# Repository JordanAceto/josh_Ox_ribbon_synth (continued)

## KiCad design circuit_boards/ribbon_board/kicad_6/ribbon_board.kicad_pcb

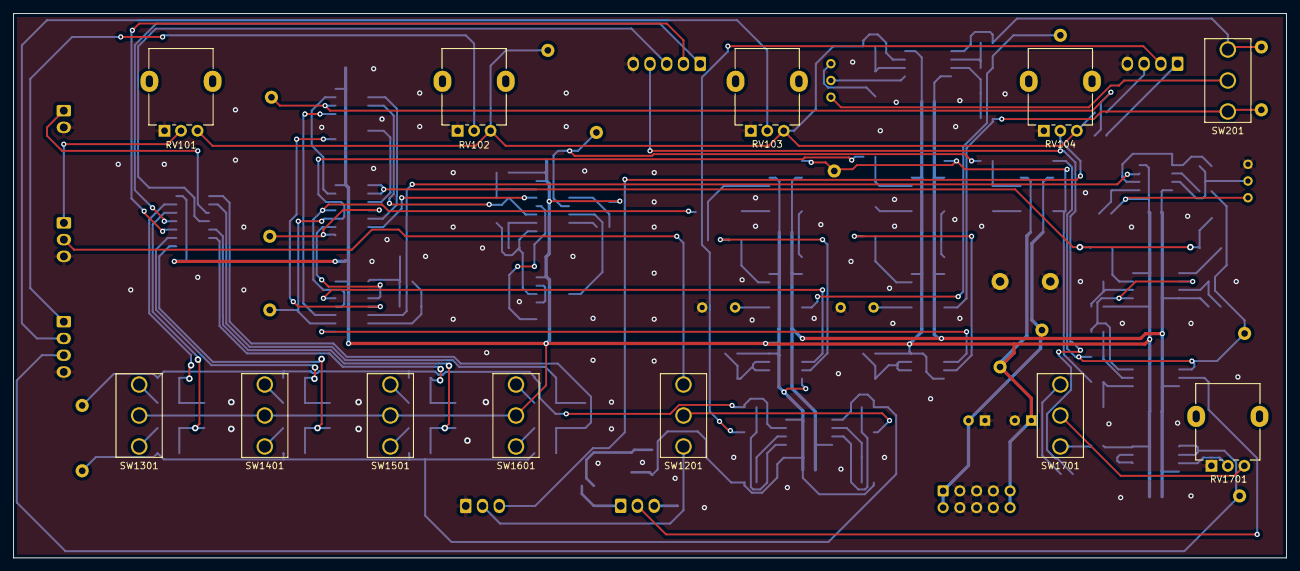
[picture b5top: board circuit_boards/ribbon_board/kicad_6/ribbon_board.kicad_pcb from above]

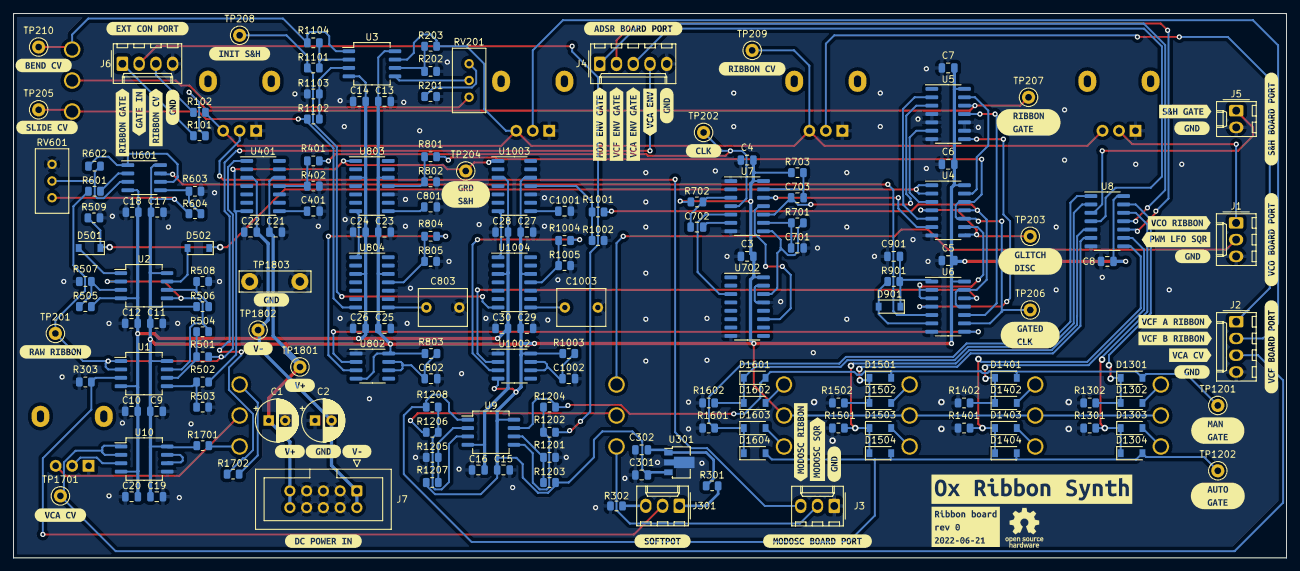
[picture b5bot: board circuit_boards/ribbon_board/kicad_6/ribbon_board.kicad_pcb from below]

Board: 2 copper layers, 193.0 x 82.5 mm, 229 parts (217 on the bottom side), 115 nets.

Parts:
C1, C2: 10u; CP_Radial_D6.3mm_P2.50mm
C3, C4, C5, C6, C7, C8, C9, C10, C11, C12, C13, C14, C15, C16, C17, C18, C19, C20, C21, C22, C23, C24, C25, C26, C27, C28, C29, C30, C302: 100n; C_0805_2012Metric
C301: 470n; C_0805_2012Metric
C401, C801, C1001: 2n2; C_0805_2012Metric
C701: 1n; C_0805_2012Metric
C702, C703: 4n7; C_0805_2012Metric
C802, C901, C1002: 10n; C_0805_2012Metric
C803, C1003: 1u; C_Rect_L7.2mm_W5.5mm_P5.00mm_FKS2_FKP2_MKS2_MKP2
D501, D502, D901, D1301, D1302, D1303, D1304, D1401, D1402, D1403, D1404, D1501, D1502, D1503, D1504, D1601, D1602, D1603, D1604: 1N4148W; D_SOD-123
J1: VCO_port; Molex_KK-254_AE-6410-03A_1x03_P2.54mm_Vertical
J2: VCF_port; Molex_KK-254_AE-6410-04A_1x04_P2.54mm_Vertical
J3: mod_osc_port; Molex_KK-254_AE-6410-03A_1x03_P2.54mm_Vertical
J4: ADSR_port; Molex_KK-254_AE-6410-05A_1x05_P2.54mm_Vertical
J5: S&H_port; Molex_KK-254_AE-6410-02A_1x02_P2.54mm_Vertical
J6: ext_port; Molex_KK-254_AE-6410-04A_1x04_P2.54mm_Vertical
J7: power_entry; IDC-Header_2x05_P2.54mm_Vertical
J301: ribbon; Molex_KK-254_AE-6410-03A_1x03_P2.54mm_Vertical
R101, R102: 1k; R_0805_2012Metric
R201, R603, R702, R703, R1201, R1202, R1205, R1206: 10k; R_0805_2012Metric
R202, R203, R303, R501, R502, R503, R504, R509, R601, R602, R604, R701, R1101, R1102, R1103, R1104, R1203, R1207, R1301, R1302, R1401, R1402, R1501, R1502, R1601, R1602, R1702: 100k; R_0805_2012Metric
R301, R302: 4k7; R_0805_2012Metric
R401, R801, R804, R1001, R1004: 5k6; R_0805_2012Metric
R402, R802, R805, R1002, R1005: 1k8; R_0805_2012Metric
R505, R506, R1701: 150k; R_0805_2012Metric
R507, R508: 470; R_0805_2012Metric
R803, R1003, R1204, R1208: 1M2; R_0805_2012Metric
R901: 120k; R_0805_2012Metric
RV101, RV102, RV103, RV104: 100k c.d.; Potentiometer_Alpha_RD901F-40-00D_Single_Vertical
RV201, RV601: 100k; Potentiometer_Bourns_3296W_Vertical
RV1701: 100k A; Potentiometer_Alpha_RD901F-40-00D_Single_Vertical
SW201, SW1201, SW1701: SW_SPDT; SPDT_mini_toggle
SW1301, SW1401, SW1501, SW1601: SW_SPDT_MSM; SPDT_mini_toggle
TP201: raw_ribbon; TestPoint_Keystone_5000-5004_Miniature
TP202: clk; TestPoint_Keystone_5000-5004_Miniature
TP203: glitch_dis; TestPoint_Keystone_5000-5004_Miniature
TP204: guard_s_and_h; TestPoint_Keystone_5000-5004_Miniature
TP205: slide_s_and_h; TestPoint_Keystone_5000-5004_Miniature
TP206: gated_clk; TestPoint_Keystone_5000-5004_Miniature
TP207: gate; TestPoint_Keystone_5000-5004_Miniature
TP208: init_s_and_h; TestPoint_Keystone_5000-5004_Miniature
TP209: ribbon_cv; TestPoint_Keystone_5000-5004_Miniature
TP210: bend_cv; TestPoint_Keystone_5000-5004_Miniature
TP1201: man_gate; TestPoint_Keystone_5000-5004_Miniature
TP1202: audo_gate; TestPoint_Keystone_5000-5004_Miniature
TP1701: vca_cv; TestPoint_Keystone_5000-5004_Miniature
TP1801: V+; TestPoint_Keystone_5000-5004_Miniature
TP1802: V-; TestPoint_Keystone_5000-5004_Miniature
TP1803: GND; TestPoint_Bridge_Pitch7.62mm_Drill1.3mm
U1, U2, U3, U9, U10: TL072; SO-8_5.3x6.2mm_P1.27mm
U4, U8: 4081; SOIC-14_3.9x8.7mm_P1.27mm
U5: 4013; SOIC-14_3.9x8.7mm_P1.27mm
U6, U7: 40106; SOIC-14_3.9x8.7mm_P1.27mm
U301: L78L10_SOT89; SOT-89-3
U401, U803, U804, U1003, U1004: LF398_SOIC14; SOIC-14_3.9x8.7mm_P1.27mm
U601: LM358; SOIC-8_3.9x4.9mm_P1.27mm
U702: 4017; SOIC-16_3.9x9.9mm_P1.27mm
U802, U1002: TLC555xD; SOIC-8_3.9x4.9mm_P1.27mm
kibuzzard-62AC7A9F: G***; kibuzzard-62AC7A9F
kibuzzard-62B1F2D1, kibuzzard-62B1F2D1#2, kibuzzard-62B1F2D1#3, kibuzzard-62B1F2D1#4, kibuzzard-62B1F2D1#5, kibuzzard-62B1F2D1#6, kibuzzard-62B1F2D1#7, kibuzzard-62B1F2D1#8: G***; kibuzzard-62B1F2D1
kibuzzard-62B1F3ED: G***; kibuzzard-62B1F3ED
kibuzzard-62B1F4B1: G***; kibuzzard-62B1F4B1
kibuzzard-62B1F4C1: G***; kibuzzard-62B1F4C1
kibuzzard-62B1F7DB: G***; kibuzzard-62B1F7DB
kibuzzard-62B1F7F1: G***; kibuzzard-62B1F7F1
kibuzzard-62B1F8A8: G***; kibuzzard-62B1F8A8
kibuzzard-62B1F8CB: G***; kibuzzard-62B1F8CB
kibuzzard-62B1F8F4: G***; kibuzzard-62B1F8F4
kibuzzard-62B1F9D0: G***; kibuzzard-62B1F9D0
kibuzzard-62B1F45D: G***; kibuzzard-62B1F45D
kibuzzard-62B1F49A: G***; kibuzzard-62B1F49A
kibuzzard-62B1F53B: G***; kibuzzard-62B1F53B
kibuzzard-62B1F72D: G***; kibuzzard-62B1F72D
kibuzzard-62B1F77F: G***; kibuzzard-62B1F77F
kibuzzard-62B1F525: G***; kibuzzard-62B1F525
kibuzzard-62B1F567: G***; kibuzzard-62B1F567
kibuzzard-62B1F712: G***; kibuzzard-62B1F712
kibuzzard-62B1F743: G***; kibuzzard-62B1F743
kibuzzard-62B1F752: G***; kibuzzard-62B1F752
kibuzzard-62B1F821: G***; kibuzzard-62B1F821
kibuzzard-62B1F904: G***; kibuzzard-62B1F904
kibuzzard-62B1F917: G***; kibuzzard-62B1F917
kibuzzard-62B1F959, kibuzzard-62B1F959#2: G***; kibuzzard-62B1F959
kibuzzard-62B1F963, kibuzzard-62B1F963#2: G***; kibuzzard-62B1F963
kibuzzard-62B1FC16: G***; kibuzzard-62B1FC16
kibuzzard-62B1FC43: G***; kibuzzard-62B1FC43
kibuzzard-62B1FC58: G***; kibuzzard-62B1FC58
kibuzzard-62B1FC81: G***; kibuzzard-62B1FC81
kibuzzard-62B1FCCC: G***; kibuzzard-62B1FCCC
kibuzzard-62B1FD45: G***; kibuzzard-62B1FD45
kibuzzard-62B1FD51: G***; kibuzzard-62B1FD51
kibuzzard-62B1FD62: G***; kibuzzard-62B1FD62
kibuzzard-62B1FDDB: G***; kibuzzard-62B1FDDB
kibuzzard-62B1FE6D: G***; kibuzzard-62B1FE6D
kibuzzard-62B1FEB0: G***; kibuzzard-62B1FEB0
kibuzzard-62B1FECC: G***; kibuzzard-62B1FECC
kibuzzard-62B235EB: G***; kibuzzard-62B235EB
kibuzzard-62B239A3: G***; kibuzzard-62B239A3
kibuzzard-62B23681: G***; kibuzzard-62B23681

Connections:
+15V: C1.1, C3.1, C4.1, C5.1, C6.1, C7.1, C8.1, C9.1, C11.1, C13.1, C15.1, C17.1, C19.1, C21.1, C23.1, C25.1, C27.1, C29.1, C301.1, J7.9, J7.10, R506.1, R604.2, R702.1, R703.1, R803.1, R1003.1, R1203.2, R1207.2, R1701.1, RV601.3, SW1301.2, SW1401.2, SW1501.2, SW1601.2, TP1801.1, U1.8 (V+), U2.8 (V+), U3.8 (V+), U4.14 (VDD), U5.14 (VDD), U6.14 (VDD), U7.14 (VDD), U8.14 (VDD), U9.8 (V+), U10.8 (V+), U301.3 (IN), U401.12 (V+), U601.8 (V+), U702.16 (VDD), U802.4 (R), U802.8 (VCC), U803.12 (V+), U804.12 (V+), U1002.4 (R), U1002.8 (VCC), U1003.12 (V+), U1004.12 (V+)
-15V: C2.2, C10.2, C12.2, C14.2, C16.2, C18.2, C20.2, C22.2, C24.2, C26.2, C28.2, C30.2, J7.1, J7.2, R505.2, TP1802.1, U1.4 (V-), U2.4 (V-), U3.4 (V-), U9.4 (V-), U10.4 (V-), U401.3 (V-), U601.4 (V-), U803.3 (V-), U804.3 (V-), U1003.3 (V-), U1004.3 (V-)
/GATE_IN: J6.2, R1202.1
/MOD_OSC_RIBBON_CTL: J3.3, RV104.2
/MOD_OSC_SQR: J3.2, SW1201.1 (A)
/PWM_LFO_SQR: J1.2, SW1201.3 (C)
/RIBBON_CV: R102.2, R203.2, RV101.3, RV102.3, RV103.3, RV104.3, TP209.1, U3.7
/RIBBON_GATE: R101.2, TP207.1, U5.12 (~Q)
/VCA_ADSR: J4.4, R1702.1
/VCA_CV: J2.3, TP1701.1, U10.1, U10.2 (-)
/VCF_A_RIBBON_CTL: J2.1, RV102.2
/VCF_B_RIBBON_CTL: J2.2, RV103.2
/VCO_RIBBON_CTL: J1.1, RV101.2
/gate_controller/MOD_ENV_GATE: J4.1, U8.11
/gate_controller/S&H_GATE: J5.1, U8.3
/gate_controller/VCA_ADSR_gate_logic/AUTO_GATE: D1304.2 (A), D1404.2 (A), D1504.2 (A), D1604.2 (A), R1208.2, TP1202.1, U9.1
/gate_controller/VCA_ADSR_gate_logic/RIBBON_GATE: D1301.2 (A), D1401.2 (A), D1501.2 (A), D1601.2 (A), R1204.2, TP1201.1, U9.7
/gate_controller/VCA_ENV_GATE: J4.3, U8.4
/gate_controller/VCF_ENV_GATE: J4.2, U8.10
/ribbon_controller/BEND_CV: R1104.2, SW201.3 (C), TP210.1, U3.1
/ribbon_controller/SLIDE_CV: R1102.1, SW201.1 (A), TP205.1, U804.7
/ribbon_controller/TRIG_0: R401.1, TP202.1, U7.4
/ribbon_controller/TRIG_9: U4.6, U7.12
/ribbon_controller/bend_scaler/INIT_IN: R1101.1, TP208.1, U1004.7
/ribbon_controller/comparator/COMP_OUT: U6.5, U601.7
/ribbon_controller/comparator/SIGNAL_IN: R501.1, R601.1, TP201.1, U1.1, U1.2 (-), U401.1 (I)
/ribbon_controller/gate_conditioner/GATED_CLK: R801.1, TP206.1, U4.10, U4.12, U6.9
/ribbon_controller/gate_conditioner/GD_IN: TP203.1, U4.4, U4.8
/ribbon_controller/gate_conditioner/S&H_TRIG: R1001.1, U4.11, U6.11, U6.13
/ribbon_controller/glitch_discriminator/S&H_RIBBON: R502.1, TP204.1, U401.7, U803.1 (I), U1003.1 (I)
/ribbon_controller/~CLK_9: C703.1, U5.3 (C), U7.10
GND: C1.2, C2.1, C3.2, C4.2, C5.2, C6.2, C7.2, C8.2, C9.2, C10.1, C11.2, C12.1, C13.2, C14.1, C15.2, C16.1, C17.2, C18.1, C19.2, C20.1, C21.2, C22.1, C23.2, C24.1, C25.2, C26.1, C27.2, C28.1, C29.2, C30.1, C301.2, C302.2, C401.2, C701.2, C801.2, C802.2, C803.2, C901.2, C1001.2, C1002.2, C1003.2, J1.3, J2.4, J3.1, J4.5, J5.2, J6.4, J7.3, J7.4, J7.5, J7.6, J7.7, J7.8, R201.2, R202.1, R302.2, R303.2, R402.2, R503.2, R507.1, R508.2, R509.2, R603.1, R802.2, R805.2, R1002.2, R1005.2, R1103.1, R1201.1, R1205.1, R1301.2, R1302.2, R1401.2, R1402.2, R1501.2, R1502.2, R1601.2, R1602.2, RV101.1, RV102.1, RV103.1, RV104.1, RV601.1, RV1701.1, TP1803.1, U4.7 (VSS), U5.4 (R), U5.5 (D), U5.7 (VSS), U5.9 (D), U5.10 (R), U6.7 (VSS), U7.1, U7.7 (VSS), U8.7 (VSS), U10.5 (+), U301.2 (GND), U401.10 (T), U702.8 (VSS), U702.13 (CKEN), U702.15 (Reset), U802.1 (GND), U803.10 (T), U804.10 (T), U1002.1 (GND), U1003.10 (T), U1004.10 (T)
unnamed: C302.1, R301.1, U301.1 (OUT)
unnamed: C401.1, U401.8 (Ch)
unnamed: C701.1, R701.1, U7.9
unnamed: C702.1, U7.6
unnamed: C702.2, R702.2, U7.3
unnamed: C703.2, R703.2, U7.13
unnamed: C801.1, U803.8 (Ch)
unnamed: C802.1, R803.2, U802.6 (THR), U802.7 (DIS)
unnamed: C803.1, U804.8 (Ch)
unnamed: C901.1, D901.1 (K), R901.2, U6.1
unnamed: C1001.1, U1003.8 (Ch)
unnamed: C1002.1, R1003.2, U1002.6 (THR), U1002.7 (DIS)
unnamed: C1003.1, U1004.8 (Ch)
unnamed: D501.1 (K), D502.1 (K), R509.1, U4.1, U4.2
unnamed: D501.2 (A), U2.1
unnamed: D502.2 (A), U2.7
unnamed: D901.2 (A), R901.1, U6.6
unnamed: D1301.1 (K), D1302.1 (K), R1302.1, U8.13
unnamed: D1302.2 (A), SW1301.3
unnamed: D1303.1 (K), D1304.1 (K), R1301.1, U8.12
unnamed: D1303.2 (A), SW1301.1
unnamed: D1401.1 (K), D1402.1 (K), R1402.1, U8.9
unnamed: D1402.2 (A), SW1401.3
unnamed: D1403.1 (K), D1404.1 (K), R1401.1, U8.8
unnamed: D1403.2 (A), SW1401.1
unnamed: D1501.1 (K), D1502.1 (K), R1502.1, U8.6
unnamed: D1502.2 (A), SW1501.3
unnamed: D1503.1 (K), D1504.1 (K), R1501.1, U8.5
unnamed: D1503.2 (A), SW1501.1
unnamed: D1601.1 (K), D1602.1 (K), R1602.1, U8.2
unnamed: D1602.2 (A), SW1601.3
unnamed: D1603.1 (K), D1604.1 (K), R1601.1, U8.1
unnamed: D1603.2 (A), SW1601.1
unnamed: J6.1, R101.1
unnamed: J6.3, R102.1
unnamed: J301.1, R301.2
unnamed: J301.2, R303.1, U1.3 (+)
unnamed: J301.3, R302.1
unnamed: R201.1, RV201.1
unnamed: R202.2, R203.1, U3.6 (-)
unnamed: R401.2, R402.1, U401.11 (Hold)
unnamed: R501.2, R504.1, U1.6 (-)
unnamed: R502.2, R503.1, U1.5 (+)
unnamed: R504.2, U1.7, U2.2 (-), U2.5 (+)
unnamed: R505.1, R507.2, U2.3 (+)
unnamed: R506.2, R508.1, U2.6 (-)
unnamed: R601.2, U601.2 (-)
unnamed: R602.1, RV601.2, U601.3 (+)
unnamed: R602.2, U601.1, U601.6 (-)
unnamed: R603.2, R604.1, U601.5 (+)
unnamed: R701.2, U7.8, U702.14 (CLK)
unnamed: R801.2, R802.1, U803.11 (Hold)
unnamed: R804.1, U802.3 (Q)
unnamed: R804.2, R805.1, U804.11 (Hold)
unnamed: R1001.2, R1002.1, U1003.11 (Hold)
unnamed: R1004.1, U1002.3 (Q)
unnamed: R1004.2, R1005.1, U1004.11 (Hold)
unnamed: R1101.2, R1104.1, U3.2 (-)
unnamed: R1102.2, R1103.2, U3.3 (+)
unnamed: R1201.2, R1203.1, U9.6 (-)
unnamed: R1202.2, R1204.1, U9.5 (+)
unnamed: R1205.2, R1207.1, U9.2 (-)
unnamed: R1206.1, SW1201.2 (B)
unnamed: R1206.2, R1208.1, U9.3 (+)
unnamed: R1701.2, SW1701.1 (A)
unnamed: R1702.2, SW1701.3 (C)
unnamed: RV201.2, U3.5 (+)
unnamed: RV201.3, SW201.2 (B)
unnamed: RV1701.2, U10.3 (+)
unnamed: RV1701.3, SW1701.2 (B)
unnamed: U4.3, U5.6 (S)
unnamed: U4.5, U5.2 (~Q)
unnamed: U4.9, U6.2, U6.3
unnamed: U4.13, U5.13 (Q)
unnamed: U5.8 (S), U6.4
unnamed: U5.11 (C), U6.10
unnamed: U6.8, U802.2 (TR)
unnamed: U7.5, U702.3 (Q0)
unnamed: U7.11, U702.11 (Q9)
unnamed: U10.6 (-), U10.7
unnamed: U803.7, U804.1 (I)
unnamed: U6.12, U1002.2 (TR)
unnamed: U1003.7, U1004.1 (I)

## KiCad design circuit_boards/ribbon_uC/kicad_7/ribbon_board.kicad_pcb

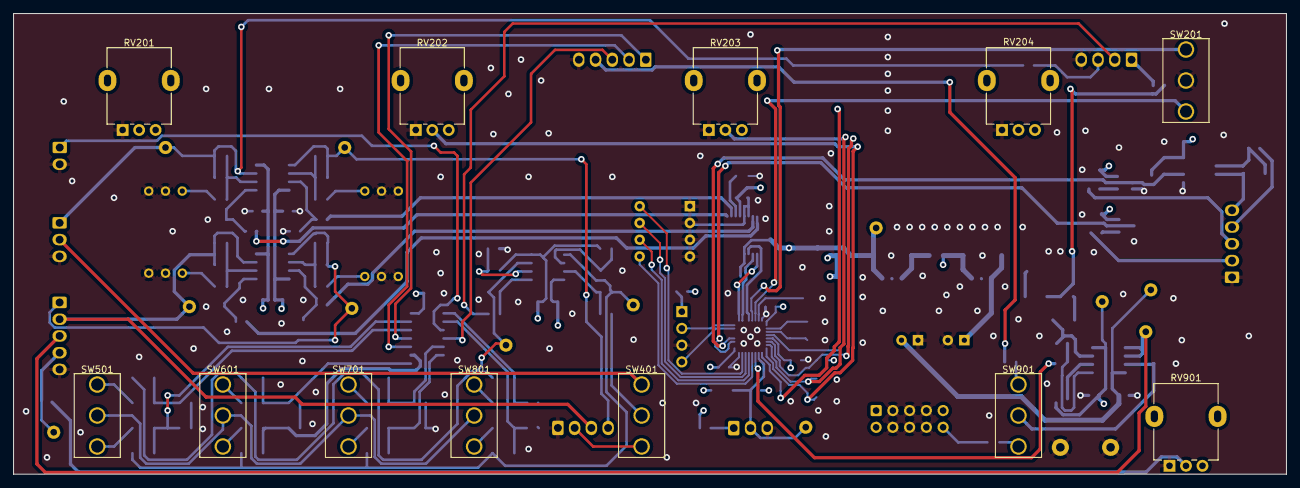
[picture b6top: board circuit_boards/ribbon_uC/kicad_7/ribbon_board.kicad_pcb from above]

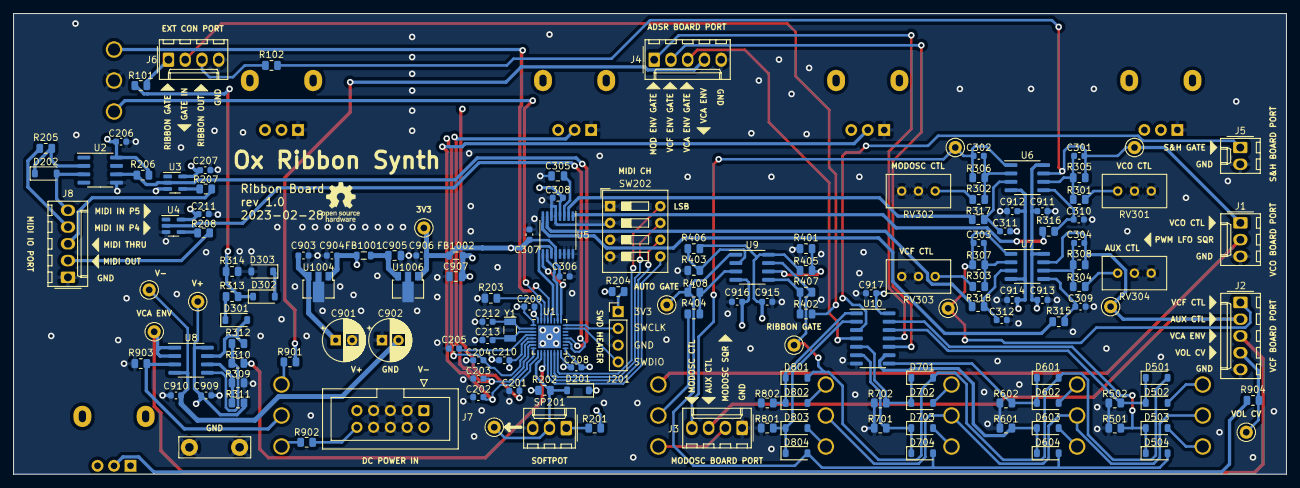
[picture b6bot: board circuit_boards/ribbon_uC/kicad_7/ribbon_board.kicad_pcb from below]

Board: 4 copper layers, 193.0 x 69.8 mm, 165 parts (153 on the bottom side), 105 nets.

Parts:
C201, C202, C203, C204, C205, C206, C207, C208, C209, C210, C211, C301, C302, C303, C304, C306, C307, C308, C309, C310, C311, C312, C903, C904, C906, C909, C910, C911, C912, C913, C914, C915, C916, C917: 100n; C_0603_1608Metric
C212, C213: 4p3; C_0603_1608Metric
C305, C907: 1u; C_0805_2012Metric
C901, C902: 10u; CP_Radial_D6.3mm_P2.50mm
C905: 2u2; C_0805_2012Metric
D201: DNF; D_SOD-123
D202, D301, D501, D502, D503, D504, D601, D602, D603, D604, D701, D702, D703, D704, D801, D802, D803, D804: 1N4148W; D_SOD-123
D302, D303: 5v1; D_SOD-123
FB1001, FB1002: 100R @ 100MHz; L_0805_2012Metric
J1: VCO_port; Molex_KK-254_AE-6410-03A_1x03_P2.54mm_Vertical
J2: VCF_port; Molex_KK-254_AE-6410-05A_1x05_P2.54mm_Vertical
J3: mod_osc_port; Molex_KK-254_AE-6410-04A_1x04_P2.54mm_Vertical
J4: ADSR_port; Molex_KK-254_AE-6410-05A_1x05_P2.54mm_Vertical
J5: S&H_port; Molex_KK-254_AE-6410-02A_1x02_P2.54mm_Vertical
J6: ext_port; Molex_KK-254_AE-6410-04A_1x04_P2.54mm_Vertical
J7: power_entry; IDC-Header_2x05_P2.54mm_Vertical
J8: MIDI_IO_port; Molex_KK-254_AE-6410-05A_1x05_P2.54mm_Vertical
J201: SWD_header; PinHeader_1x04_P2.54mm_Vertical
R101, R102, R204, R313, R904: 1k; R_0805_2012Metric
R201: 22; R_0805_2012Metric
R202: DNF; R_0805_2012Metric
R203, R206, R309, R310, R401, R402, R403, R404: 10k; R_0805_2012Metric
R205: 220; R_0805_2012Metric
R207, R208: 47; R_0805_2012Metric
R301, R302, R303, R304: 4k7; R_0805_2012Metric
R305, R306, R307, R308, R315, R316, R317, R318: 12k; R_0805_2012Metric
R311, R314, R405, R406, R501, R502, R601, R602, R701, R702, R801, R802, R903: 100k; R_0805_2012Metric
R312, R407, R408: 1M2; R_0805_2012Metric
R901: 82k; R_0805_2012Metric
R902: 200k; R_0805_2012Metric
RV201, RV204: 10k; Potentiometer_Alpha_RD901F-40-00D_Single_Vertical
RV202, RV203: 10k c.d.; Potentiometer_Alpha_RD901F-40-00D_Single_Vertical
RV301, RV302, RV303, RV304: 5k; Potentiometer_Bourns_3296W_Vertical
RV901: 100k; Potentiometer_Alpha_RD901F-40-00D_Single_Vertical
SP201: softpot; Molex_KK-254_AE-6410-03A_1x03_P2.54mm_Vertical
SW201, SW501, SW601, SW701, SW801: SW_SPDT_MSM; SPDT_mini_toggle
SW202: MIDI_CH; SW_DIP_SPSTx04_Slide_9.78x12.34mm_W7.62mm_P2.54mm
SW401, SW901: SW_SPDT; SPDT_mini_toggle
TP201: RAW_RIBBON; TestPoint_Keystone_5000-5004_Miniature
TP301: VCO_RIBBON; TestPoint_Keystone_5000-5004_Miniature
TP302: MODOSC_RIBBON; TestPoint_Keystone_5000-5004_Miniature
TP303: VCF_RIBBON; TestPoint_Keystone_5000-5004_Miniature
TP304: AUX_CV; TestPoint_Keystone_5000-5004_Miniature
TP401: rib_gate; TestPoint_Keystone_5000-5004_Miniature
TP402: auto_gate; TestPoint_Keystone_5000-5004_Miniature
TP901: VCA_ADSR_CV; TestPoint_Keystone_5000-5004_Miniature
TP902: VCA_VOL_CV; TestPoint_Keystone_5000-5004_Miniature
TP1001: V+; TestPoint_Keystone_5000-5004_Miniature
TP1002: V-; TestPoint_Keystone_5000-5004_Miniature
TP1003: GND; TestPoint_Bridge_Pitch7.62mm_Drill1.3mm
TP1004: 3v3; TestPoint_Keystone_5000-5004_Miniature
U1: STM32L412K8Ux; QFN-32-1EP_5x5mm_P0.5mm_EP3.45x3.45mm
U2: VO0600T; SOIC-8_3.9x4.9mm_P1.27mm
U3, U4: SN74LV1T34DBV; SOT-23-5
U5: DAC8164; TSSOP-16_4.4x5mm_P0.65mm
U6, U7, U8, U9: TL072; SOIC-8_3.9x4.9mm_P1.27mm
U10: 4081; SOIC-14_3.9x8.7mm_P1.27mm
U1004: L78L05_SOT89; SOT-89-3
U1006: L78L33_SOT89; SOT-89-3
Y1: 32_768KHZ; Crystal_SMD_MicroCrystal_CC7V-T1A-2Pin_3.2x1.5mm

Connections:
+3.3V: C206.1, C207.1, C208.1, C209.1, C211.1, C306.1, C307.1, C906.1, D201.1 (K), FB1002.1, R204.1, R206.1, TP1004.1, U1.1 (VDD), U1.17 (VDD), U2.8 (VCC), U3.5 (VCC), U4.5 (VCC), U5.12 (IOVDD), U1006.1 (OUT)
+3.3VA: C210.1, C308.1, C907.1, FB1002.2, R201.1, RV201.3, RV202.3, RV203.3, RV204.3, U1.5 (VDDA), U5.4 (AVDD)
+5V: C904.1, FB1001.1, R202.1, RV901.3, U1004.1 (OUT)
+15V: C901.1, C903.1, C909.1, C911.1, C913.1, C915.1, C917.1, J7.9, J7.10, R311.2, R405.2, R406.2, R902.1, SW501.2, SW601.2, SW701.2, SW801.2, TP1001.1, U6.8 (V+), U7.8 (V+), U8.8 (V+), U9.8 (V+), U10.14 (VDD), U1004.3 (IN)
-15V: C902.2, C910.2, C912.2, C914.2, C916.2, J7.1, J7.2, TP1002.1, U6.4 (V-), U7.4 (V-), U8.4 (V-), U9.4 (V-)
/EXT_GATE_IN_NORMAL_TO_RIBBON_GATE: J6.2, R402.1
/MOD_OSC_SQR: J3.2, SW401.1 (A)
/OPT_VCF_BBD_CV: C304.2, J2.2, J3.3, R308.2, TP304.1, U7.7
/PWM_LFO_SQR: J1.2, SW401.3 (C)
/VCA_ADSR: J4.4, R901.1
/VCA_ENV_CV: J2.3, TP901.1, U8.1, U8.2 (-)
/VCA_VOL_CV: J2.4, R904.2, TP902.1
/VCO_RIBBON_CTL: C301.2, J1.1, R102.2, R305.2, TP301.1, U6.7
/digital_ribbon_control/GATE_3V3: R310.1, U1.11 (PA5)
/digital_ribbon_control/GLIDE_CV: C204.1, RV204.2, U1.6 (PA0)
/digital_ribbon_control/MIDI_CH_0: SW202.8, U1.15 (PB1)
/digital_ribbon_control/MIDI_CH_1: SW202.7, U1.14 (PB0)
/digital_ribbon_control/MIDI_CH_2: SW202.6, U1.13 (PA7)
/digital_ribbon_control/MIDI_CH_3: SW202.5, U1.12 (PA6)
/digital_ribbon_control/MIDI_IN_P4: J8.4, R205.1
/digital_ribbon_control/MIDI_IN_P5: D202.2 (A), J8.5, U2.3 (C)
/digital_ribbon_control/MIDI_OUT: J8.2, R208.2
/digital_ribbon_control/MIDI_RX: R206.2, U1.20 (PA10), U2.6 (VO), U3.2 (A)
/digital_ribbon_control/MIDI_THRU: J8.3, R207.2
/digital_ribbon_control/MIDI_TX: U1.19 (PA9), U4.2 (A)
/digital_ribbon_control/MODE_SW_1: SW201.1, U1.29 (PB6)
/digital_ribbon_control/MODE_SW_2: SW201.3, U1.30 (PB7)
/digital_ribbon_control/MODOSC_LEV: C202.1, RV202.2, U1.8 (PA2)
/digital_ribbon_control/RAW_RIBBON: D201.2 (A), R202.2, SP201.2, TP201.1, U1.10 (PA4)
/digital_ribbon_control/SPI_CS: U1.25 (PA15), U5.9 (~SYNC)
/digital_ribbon_control/SPI_SCK: U1.26 (PB3), U5.10 (SCLK)
/digital_ribbon_control/SPI_SDO: U1.28 (PB5), U5.11 (DIN)
/digital_ribbon_control/SYS_SWCLK: J201.2, U1.24 (PA14)
/digital_ribbon_control/SYS_SWDIO: J201.4, U1.23 (PA13)
/digital_ribbon_control/VCF_LEV: C203.1, RV203.2, U1.7 (PA1)
/digital_ribbon_control/VCO_LEV: C201.1, RV201.2, U1.9 (PA3)
/gate_controller/MOD_ENV_GATE: J4.1, U10.11
/gate_controller/S&H_GATE: J5.1, U10.3
/gate_controller/VCA_ADSR_gate_logic/AUTO_GATE: D504.2 (A), D604.2 (A), D704.2 (A), D804.2 (A), R408.2, TP402.1, U9.1
/gate_controller/VCA_ADSR_gate_logic/RIBBON_GATE: D501.2 (A), D601.2 (A), D701.2 (A), D801.2 (A), R407.2, TP401.1, U9.7
/gate_controller/VCA_ENV_GATE: J4.3, U10.4
/gate_controller/VCF_ENV_GATE: J4.2, U10.10
/ribbon_scalers/GATE: D302.1 (K), R101.2, R313.2, R314.1
/ribbon_scalers/MODOSC_CTL_OUT: C302.2, J3.4, R306.2, TP302.1, U6.1
/ribbon_scalers/VCF_CTL_OUT: C303.2, J2.1, R307.2, TP303.1, U7.1
GND: C201.2, C202.2, C203.2, C204.2, C205.1, C206.2, C207.2, C208.2, C209.2, C210.2, C211.2, C212.1, C213.1, C305.2, C306.2, C307.2, C308.2, C309.1, C310.1, C311.1, C312.1, C901.2, C902.1, C903.2, C904.2, C905.2, C906.2, C907.2, C909.2, C910.1, C911.2, C912.1, C913.2, C914.1, C915.2, C916.1, C917.2, D303.2 (A), J1.3, J2.5, J3.1, J4.5, J5.2, J6.4, J7.3, J7.4, J7.5, J7.6, J7.7, J7.8, J8.1, J201.3, R203.1, R309.1, R314.2, R401.1, R403.1, R501.2, R502.2, R601.2, R602.2, R701.2, R702.2, R801.2, R802.2, R903.1, RV201.1, RV202.1, RV203.1, RV204.1, RV301.2, RV301.3, RV302.2, RV302.3, RV303.2, RV303.3, RV304.2, RV304.3, RV901.1, SP201.3, SW201.2, SW202.1, SW202.2, SW202.3, SW202.4, TP1003.1, U1.16 (VSS), U1.32 (VSS), U1.33 (VSS), U2.5 (GND), U3.3 (GND), U4.3 (GND), U5.5 (VREFL), U5.6 (GND), U5.13 (A0), U5.14 (A1), U5.15 (~ENABLE), U5.16 (LDAC), U10.7 (VSS), U1004.2 (GND), U1006.2 (GND)
unnamed: C905.1, FB1001.2, U1006.3 (IN)
unnamed: D202.1 (K), R205.2, U2.2 (A)
unnamed: D301.2 (A), R312.2, U8.7
unnamed: D301.1 (K), R313.1
unnamed: D302.2 (A), D303.1 (K)
unnamed: D501.1 (K), D502.1 (K), R502.1, U10.12
unnamed: D502.2 (A), SW501.3
unnamed: D503.2 (A), SW501.1
unnamed: D503.1 (K), D504.1 (K), R501.1, U10.13
unnamed: D601.1 (K), D602.1 (K), R602.1, U10.8
unnamed: D602.2 (A), SW601.3
unnamed: D603.2 (A), SW601.1
unnamed: D603.1 (K), D604.1 (K), R601.1, U10.9
unnamed: D701.1 (K), D702.1 (K), R702.1, U10.5
unnamed: D702.2 (A), SW701.3
unnamed: D703.2 (A), SW701.1
unnamed: D703.1 (K), D704.1 (K), R701.1, U10.6
unnamed: D801.1 (K), D802.1 (K), R802.1, U10.1
unnamed: D802.2 (A), SW801.3
unnamed: D803.2 (A), SW801.1
unnamed: D803.1 (K), D804.1 (K), R801.1, U10.2
unnamed: J6.1, R101.1
unnamed: J6.3, R102.1
unnamed: J201.1, R204.2
unnamed: R301.1, RV301.1
unnamed: R302.1, RV302.1
unnamed: R303.1, RV303.1
unnamed: R304.1, RV304.1
unnamed: R904.1, RV901.2
unnamed: R201.2, SP201.1
unnamed: R404.1, SW401.2 (B)
unnamed: R902.2, SW901.1 (A)
unnamed: R903.2, SW901.2 (B), U8.3 (+)
unnamed: R901.2, SW901.3 (C)
unnamed: C205.2, U1.4 (NRST)
unnamed: C212.2, U1.2 (PC14), Y1.1
unnamed: C213.2, U1.3 (PC15), Y1.2
unnamed: R203.2, U1.31 (PH3)
unnamed: R207.1, U3.4 (Y)
unnamed: R208.1, U4.4 (Y)
unnamed: R316.1, U5.1 (VOUTA)
unnamed: R317.1, U5.2 (VOUTB)
unnamed: R318.1, U5.7 (VOUTC)
unnamed: R315.1, U5.8 (VOUTD)
unnamed: C305.1, U5.3 (VREFH/VREFOUT)
unnamed: C311.2, R317.2, U6.3 (+)
unnamed: C302.1, R302.2, R306.1, U6.2 (-)
unnamed: C310.2, R316.2, U6.5 (+)
unnamed: C301.1, R301.2, R305.1, U6.6 (-)
unnamed: C312.2, R318.2, U7.3 (+)
unnamed: C303.1, R303.2, R307.1, U7.2 (-)
unnamed: C309.2, R315.2, U7.5 (+)
unnamed: C304.1, R304.2, R308.1, U7.6 (-)
unnamed: R310.2, R312.1, U8.5 (+)
unnamed: R309.2, R311.1, U8.6 (-)
unnamed: R404.2, R408.1, U9.3 (+)
unnamed: R403.2, R406.1, U9.2 (-)
unnamed: R402.2, R407.1, U9.5 (+)
unnamed: R401.2, R405.1, U9.6 (-)

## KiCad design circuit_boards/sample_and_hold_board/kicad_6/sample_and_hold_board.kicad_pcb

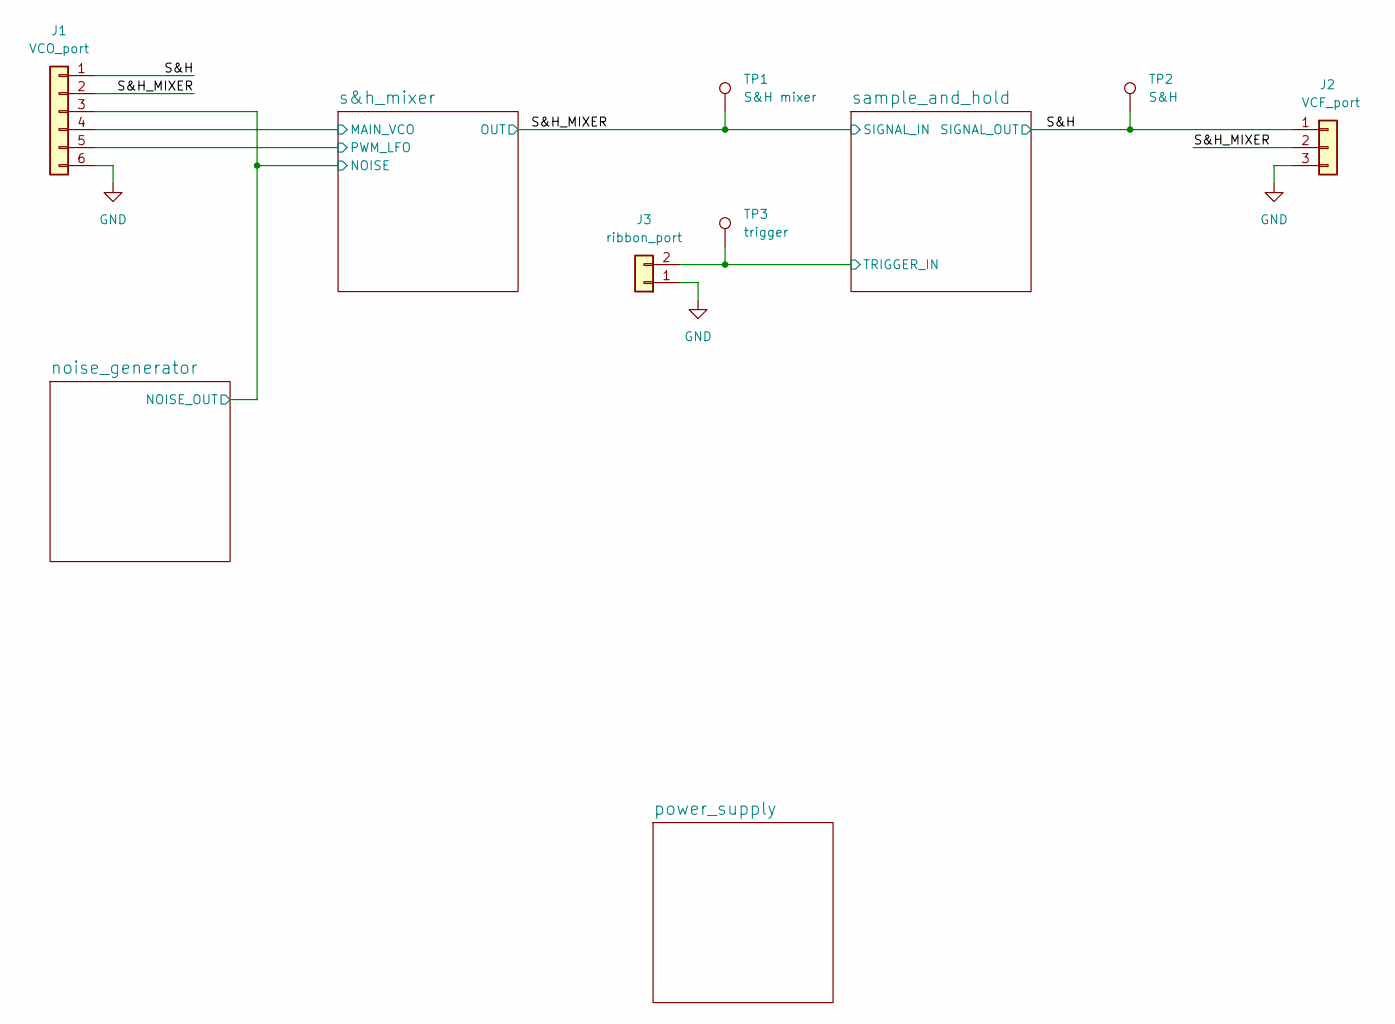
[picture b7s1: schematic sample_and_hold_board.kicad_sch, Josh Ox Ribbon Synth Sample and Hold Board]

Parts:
J1: VCO_port; Molex_KK-254_AE-6410-06A_1x06_P2.54mm_Vertical
J2: VCF_port; Molex_KK-254_AE-6410-03A_1x03_P2.54mm_Vertical
J3: ribbon_port; Molex_KK-254_AE-6410-02A_1x02_P2.54mm_Vertical
TP1: S&H mixer; TestPoint_Keystone_5000-5004_Miniature
TP2: S&H; TestPoint_Keystone_5000-5004_Miniature
TP3: trigger; TestPoint_Keystone_5000-5004_Miniature

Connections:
/S&H: J1.1, J2.1, TP2.1; also elsewhere on the board
/S&H_MIXER: J1.2, J2.2, TP1.1; also elsewhere on the board
/noise_generator/NOISE_OUT: J1.3; also elsewhere on the board
/s&h_mixer/MAIN_VCO: J1.4; also elsewhere on the board
/s&h_mixer/PWM_LFO: J1.5; also elsewhere on the board
/sample_and_hold/TRIGGER_IN: J3.2, TP3.1; also elsewhere on the board
GND: J1.6, J2.3, J3.1; also elsewhere on the board

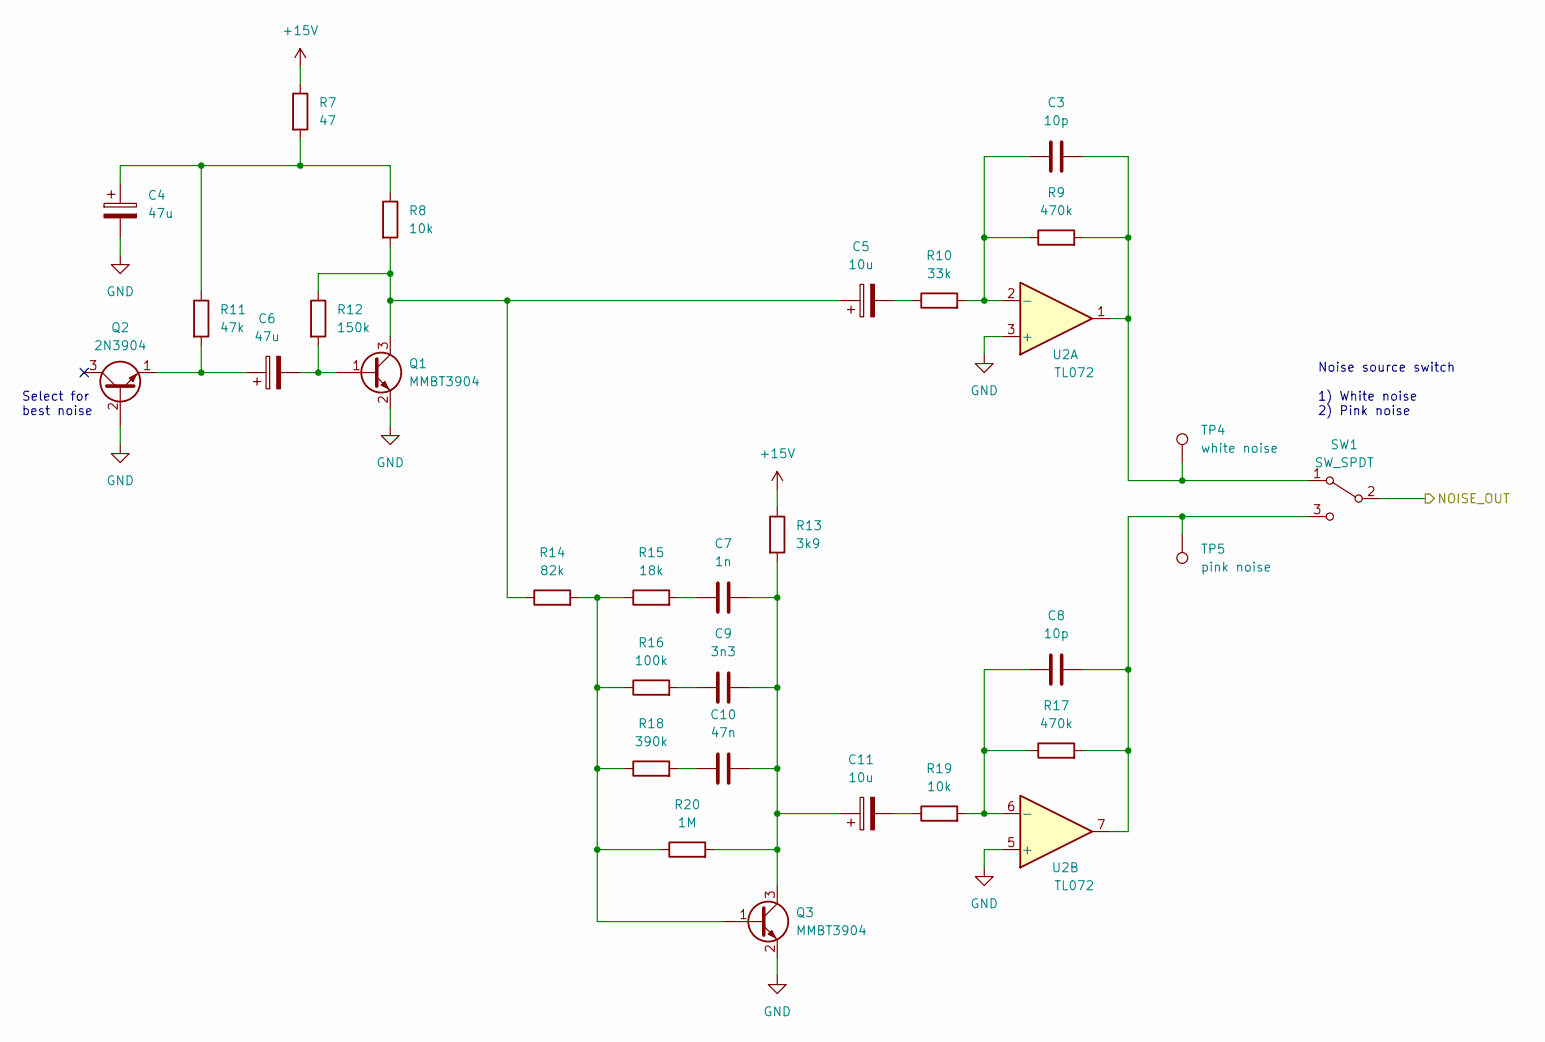
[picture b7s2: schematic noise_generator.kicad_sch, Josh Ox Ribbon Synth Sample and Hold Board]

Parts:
C3, C8: 10p; C_0805_2012Metric
C4, C6: 47u; CP_Radial_D6.3mm_P2.50mm
C5, C11: 10u; CP_Radial_D6.3mm_P2.50mm
C7: 1n; C_0805_2012Metric
C9: 3n3; C_0805_2012Metric
C10: 47n; C_0805_2012Metric
Q1, Q3: MMBT3904; SOT-23
Q2: 2N3904; TO-92_Inline_Wide
R7: 47; R_0805_2012Metric
R8, R19: 10k; R_0805_2012Metric
R9, R17: 470k; R_0805_2012Metric
R10: 33k; R_0805_2012Metric
R11: 47k; R_0805_2012Metric
R12: 150k; R_0805_2012Metric
R13: 3k9; R_0805_2012Metric
R14: 82k; R_0805_2012Metric
R15: 18k; R_0805_2012Metric
R16: 100k; R_0805_2012Metric
R18: 390k; R_0805_2012Metric
R20: 1M; R_0805_2012Metric
SW1: SW_SPDT; SPDT_mini_toggle
TP4: white noise; TestPoint_Keystone_5000-5004_Miniature
TP5: pink noise; TestPoint_Keystone_5000-5004_Miniature
U2: TL072; SO-8_5.3x6.2mm_P1.27mm

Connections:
+15V: R7.1, R13.1; also elsewhere on the board
/noise_generator/NOISE_OUT: SW1.2 (B); also elsewhere on the board
GND: C4.2, Q1.2 (E), Q2.2 (B), Q3.2 (E), U2.3 (+), U2.5 (+); also elsewhere on the board
unnamed: C3.1, R9.1, R10.2, U2.2 (-)
unnamed: C3.2, R9.2, SW1.1 (A), TP4.1, U2.1
unnamed: C4.1, R7.2, R8.1, R11.1
unnamed: C5.1, Q1.3 (C), R8.2, R12.1, R14.1
unnamed: C5.2, R10.1
unnamed: C6.1, Q2.1 (E), R11.2
unnamed: C6.2, Q1.1 (B), R12.2
unnamed: C7.1, R15.2
unnamed: C8.1, R17.1, R19.2, U2.6 (-)
unnamed: C8.2, R17.2, SW1.3 (C), TP5.1, U2.7
unnamed: C9.1, R16.2
unnamed: C10.1, R18.2
unnamed: C7.2, C9.2, C10.2, C11.1, Q3.3 (C), R13.2, R20.2
unnamed: C11.2, R19.1
unnamed: Q3.1 (B), R14.2, R15.1, R16.1, R18.1, R20.1

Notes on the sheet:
Noise source switch 1) White noise 2) Pink noise
Select for best noise

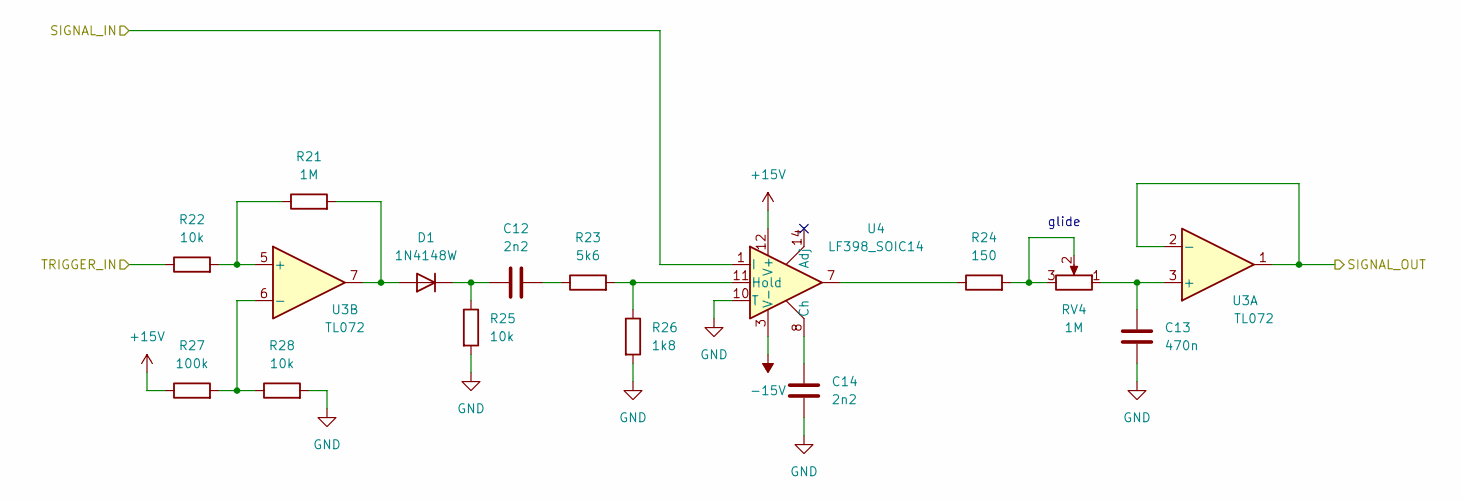
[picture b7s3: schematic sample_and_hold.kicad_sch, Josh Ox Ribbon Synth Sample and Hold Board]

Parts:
C12: 2n2; C_0805_2012Metric
C13: 470n; C_Rect_L7.2mm_W5.5mm_P5.00mm_FKS2_FKP2_MKS2_MKP2
C14: 2n2; C_Rect_L7.2mm_W2.5mm_P5.00mm_FKS2_FKP2_MKS2_MKP2
D1: 1N4148W; D_SOD-123
R21: 1M; R_0805_2012Metric
R22, R25, R28: 10k; R_0805_2012Metric
R23: 5k6; R_0805_2012Metric
R24: 150; R_0805_2012Metric
R26: 1k8; R_0805_2012Metric
R27: 100k; R_0805_2012Metric
RV4: 1M; Potentiometer_Alpha_RD901F-40-00D_Single_Vertical
U3: TL072; SO-8_5.3x6.2mm_P1.27mm
U4: LF398_SOIC14; SOIC-14_3.9x8.7mm_P1.27mm

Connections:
+15V: R27.1, U4.12 (V+); also elsewhere on the board
-15V: U4.3 (V-); also elsewhere on the board
/S&H: U3.1, U3.2 (-); also elsewhere on the board
/S&H_MIXER: U4.1 (I); also elsewhere on the board
/sample_and_hold/TRIGGER_IN: R22.1; also elsewhere on the board
GND: C13.2, C14.2, R25.2, R26.2, R28.2, U4.10 (T); also elsewhere on the board
unnamed: C12.1, D1.1 (K), R25.1
unnamed: C12.2, R23.1
unnamed: C13.1, RV4.1, U3.3 (+)
unnamed: C14.1, U4.8 (Ch)
unnamed: D1.2 (A), R21.2, U3.7
unnamed: R21.1, R22.2, U3.5 (+)
unnamed: R23.2, R26.1, U4.11 (Hold)
unnamed: R24.1, U4.7
unnamed: R24.2, RV4.2, RV4.3
unnamed: R27.2, R28.1, U3.6 (-)

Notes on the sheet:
glide
